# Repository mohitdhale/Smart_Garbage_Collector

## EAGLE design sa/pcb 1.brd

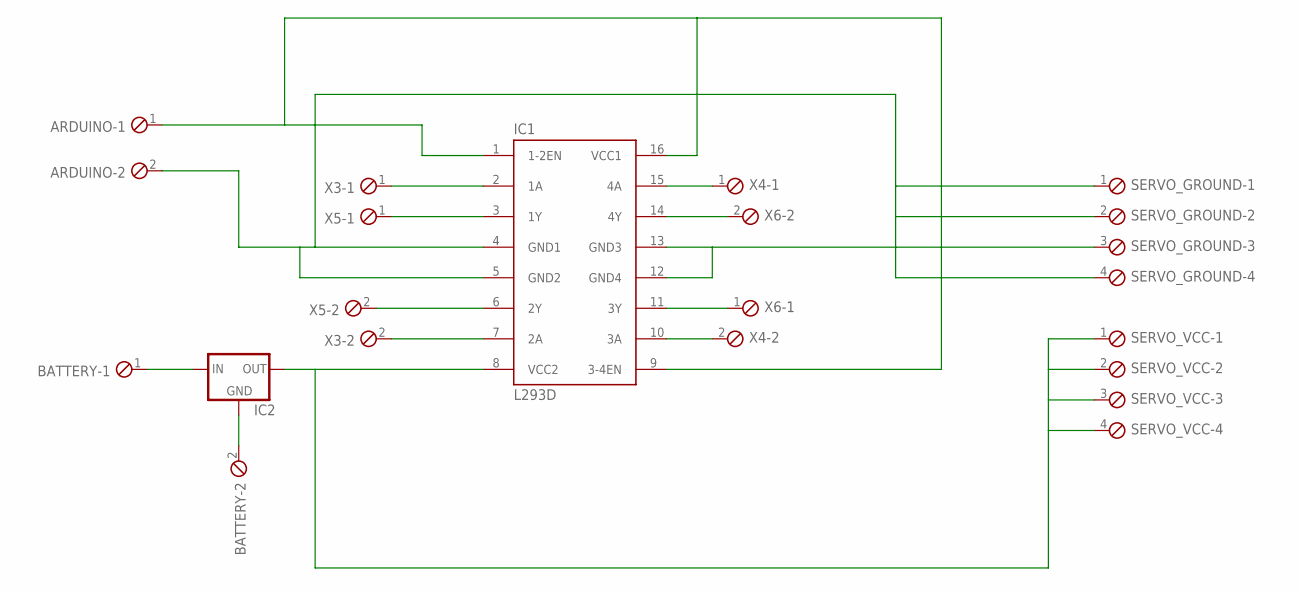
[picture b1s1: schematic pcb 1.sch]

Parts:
ARDUINO: MPT2; 2POL254
BATTERY: MPT2; 2POL254
IC1: L293D; DIL16
IC2: 78MXXS
SERVO_GROUND: MPT4; 4POL254
SERVO_VCC: MPT4; 4POL254
X3, X4, X5, X6: MPT2; 2POL254

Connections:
unnamed: IC1.2 (1A), X3.1
unnamed: IC1.7 (2A), X3.2
unnamed: IC1.15 (4A), X4.1
unnamed: IC1.10 (3A), X4.2
unnamed: IC1.14 (4Y), X6.2
unnamed: IC1.11 (3Y), X6.1
unnamed: IC1.3 (1Y), X5.1
unnamed: IC1.6 (2Y), X5.2
unnamed: BATTERY.1, IC2.IN
unnamed: BATTERY.2, IC2.GND
unnamed: IC1.8 (VCC2), IC2.OUT, SERVO_VCC.1, SERVO_VCC.2, SERVO_VCC.3, SERVO_VCC.4
unnamed: ARDUINO.2, IC1.4 (GND1), IC1.5 (GND2), IC1.12 (GND4), IC1.13 (GND3), SERVO_GROUND.1, SERVO_GROUND.2, SERVO_GROUND.3, SERVO_GROUND.4
unnamed: ARDUINO.1, IC1.1 (1-2EN), IC1.9 (3-4EN), IC1.16 (VCC1)

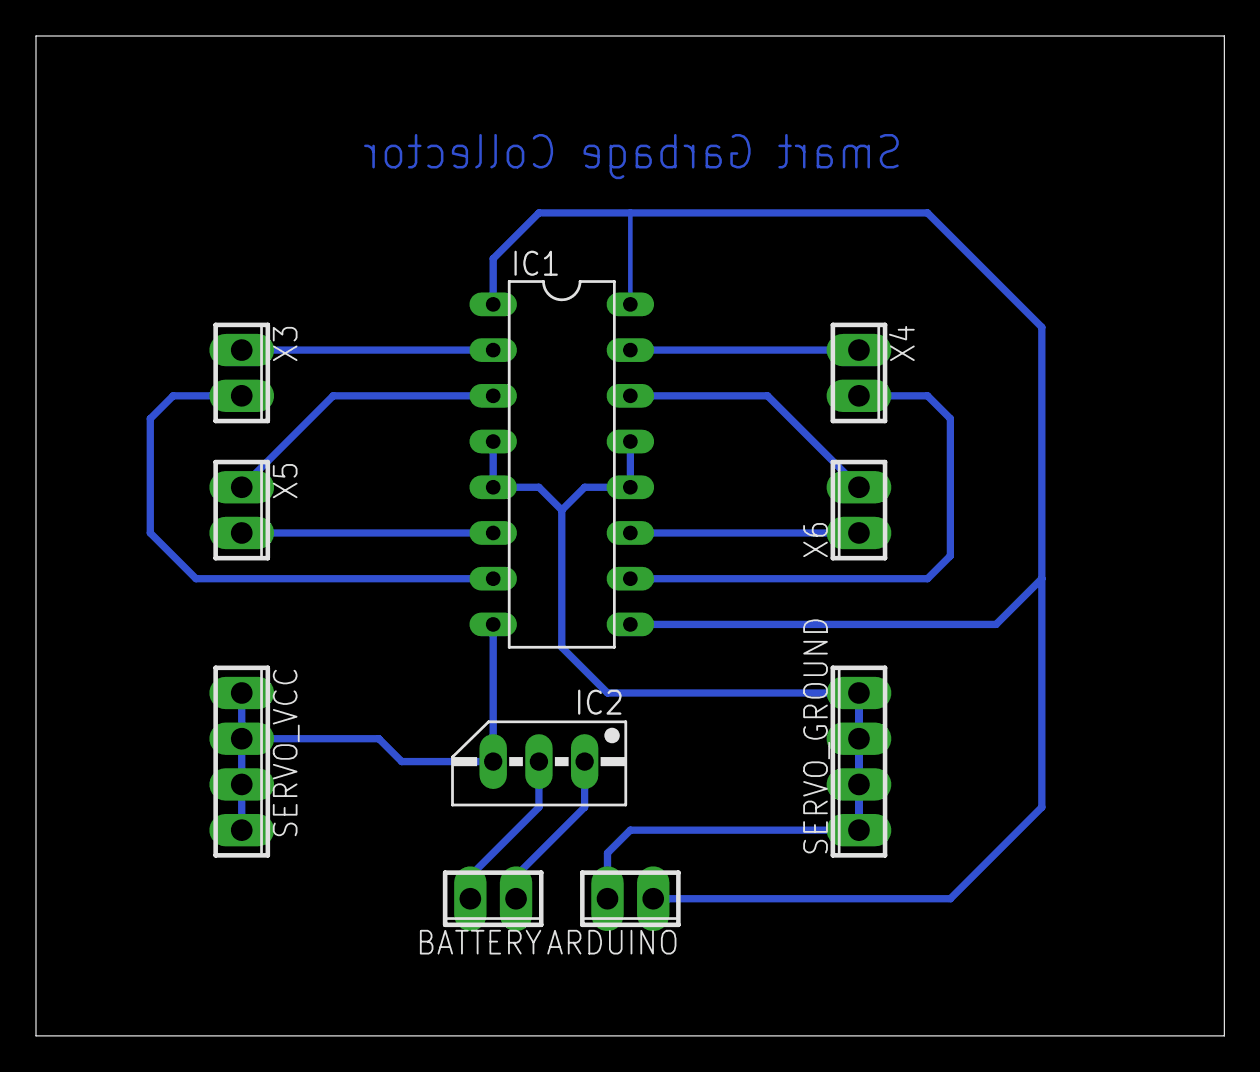
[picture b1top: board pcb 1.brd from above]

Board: 2 copper layers, 66.0 x 55.5 mm, 10 parts (0 on the bottom side), 13 nets.

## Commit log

2021-02-22 initialize
